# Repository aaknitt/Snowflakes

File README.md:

# ESP8266 Snowflakes
**KiCAD and FreeCAD files for RGB(W) snowflakes**

KiCAD schematic and PCB layout files (along with associated Gerber files) for ESP8266-based RGB(W) snowflakes.  

FreeCAD files for 3D printed diffuser (use clear filament).

Each snowflake uses 25 SK6812 (for RGBW) or WS2812b pixels.
Can be operated using the fantastic [ESPixelStick firmware](https://github.com/forkineye/ESPixelStick) in conjunction with a program such as XLights64.

Unmodified ESPixelStick firmware should work with RBG pixels.

If using RGBW pixels, modified firmware is necessary (I may put up a fork at some point in the future).

**Note:**  I have not actually made a batch of PCBs from these exact files.  I built PCBs using an earlier version, and these files include all of the changes I've made to correct mistakes in the original batch.  Use at your own risk!

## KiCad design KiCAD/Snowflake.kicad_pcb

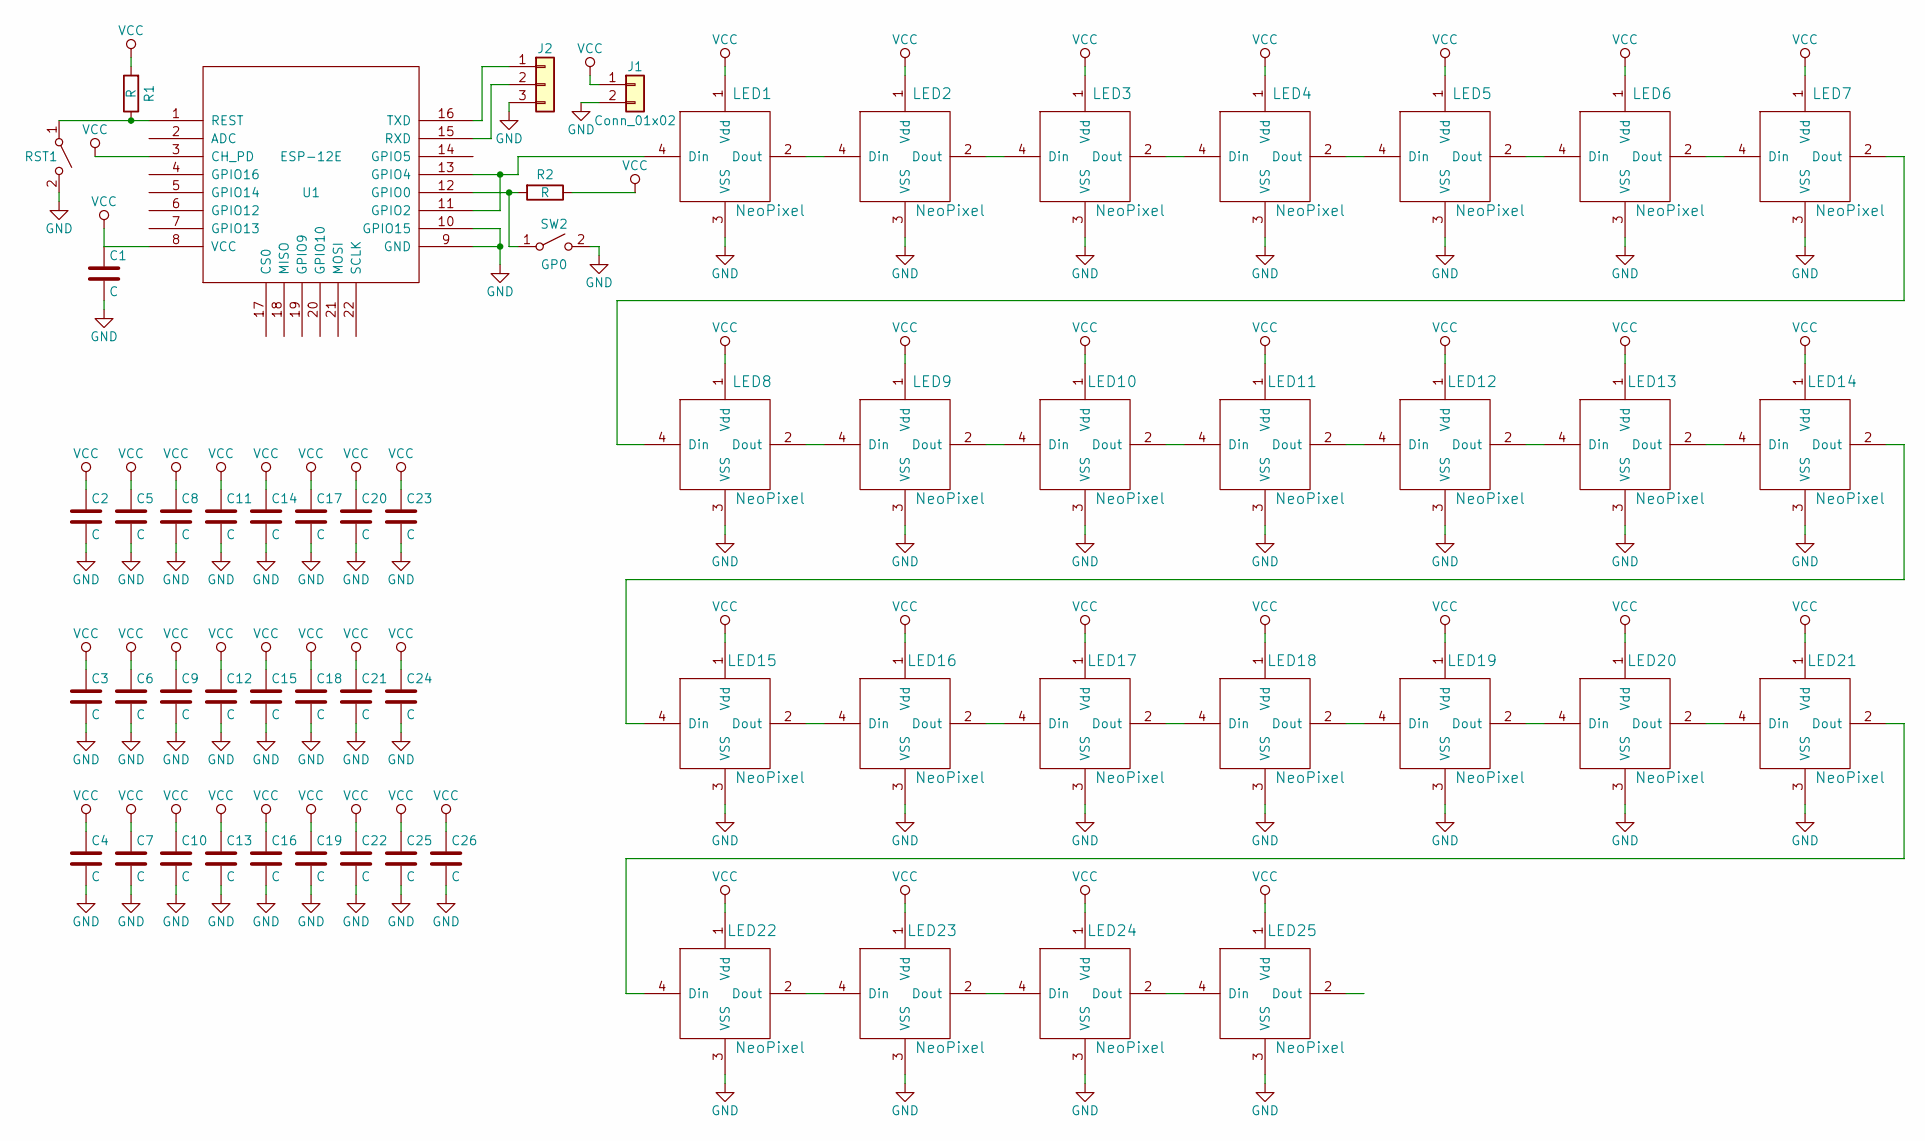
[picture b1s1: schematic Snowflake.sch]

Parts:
C1, C2, C3, C4, C5, C6, C7, C8, C9, C10, C11, C12, C13, C14, C15, C16, C17, C18, C19, C20, C21, C22, C23, C24, C25, C26: C; C_0805_HandSoldering
J1: Conn_01x02; SolderWirePad_2x_1-2mmDrill
J2: Conn_01x03; Pin_Header_Straight_1x03_Pitch2.54mm
LED1, LED2, LED3, LED4, LED5, LED6, LED7, LED8, LED9, LED10, LED11, LED12, LED13, LED14, LED15, LED16, LED17, LED18, LED19, LED20, LED21, LED22, LED23, LED24, LED25: NeoPixel; LED_WS2812B-PLCC4
R1, R2: R; R_0805_HandSoldering
RST1: SW_SPST; SW_SPST_KMR2
SW2: GP0; SW_SPST_KMR2
U1: ESP-12E; ESP-12E_SMD

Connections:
GND: C1.2, C2.2, C3.2, C4.2, C5.2, C6.2, C7.2, C8.2, C9.2, C10.2, C11.2, C12.2, C13.2, C14.2, C15.2, C16.2, C17.2, C18.2, C19.2, C20.2, C21.2, C22.2, C23.2, C24.2, C25.2, C26.2, J1.2, J2.3, LED1.3 (VSS), LED2.3 (VSS), LED3.3 (VSS), LED4.3 (VSS), LED5.3 (VSS), LED6.3 (VSS), LED7.3 (VSS), LED8.3 (VSS), LED9.3 (VSS), LED10.3 (VSS), LED11.3 (VSS), LED12.3 (VSS), LED13.3 (VSS), LED14.3 (VSS), LED15.3 (VSS), LED16.3 (VSS), LED17.3 (VSS), LED18.3 (VSS), LED19.3 (VSS), LED20.3 (VSS), LED21.3 (VSS), LED22.3 (VSS), LED23.3 (VSS), LED24.3 (VSS), LED25.3 (VSS), RST1.2 (B), SW2.2 (B), U1.9 (GND), U1.10 (GPIO15)
unnamed: J2.1, U1.16 (TXD)
unnamed: J2.2, U1.15 (RXD)
unnamed: LED1.2 (Dout), LED2.4 (Din)
unnamed: LED1.4 (Din), U1.11 (GPIO2), U1.13 (GPIO4)
unnamed: LED2.2 (Dout), LED3.4 (Din)
unnamed: LED3.2 (Dout), LED4.4 (Din)
unnamed: LED4.2 (Dout), LED5.4 (Din)
unnamed: LED5.2 (Dout), LED6.4 (Din)
unnamed: LED6.2 (Dout), LED7.4 (Din)
unnamed: LED7.2 (Dout), LED8.4 (Din)
unnamed: LED8.2 (Dout), LED9.4 (Din)
unnamed: LED10.2 (Dout), LED11.4 (Din)
unnamed: LED9.2 (Dout), LED10.4 (Din)
unnamed: LED11.2 (Dout), LED12.4 (Din)
unnamed: LED12.2 (Dout), LED13.4 (Din)
unnamed: LED13.2 (Dout), LED14.4 (Din)
unnamed: LED14.2 (Dout), LED15.4 (Din)
unnamed: LED15.2 (Dout), LED16.4 (Din)
unnamed: LED16.2 (Dout), LED17.4 (Din)
unnamed: LED17.2 (Dout), LED18.4 (Din)
unnamed: LED18.2 (Dout), LED19.4 (Din)
unnamed: LED19.2 (Dout), LED20.4 (Din)
unnamed: LED20.2 (Dout), LED21.4 (Din)
unnamed: LED21.2 (Dout), LED22.4 (Din)
unnamed: LED22.2 (Dout), LED23.4 (Din)
unnamed: LED23.2 (Dout), LED24.4 (Din)
unnamed: LED24.2 (Dout), LED25.4 (Din)
unnamed: R1.1, RST1.1 (A), U1.1 (REST)
unnamed: R2.2, SW2.1 (A), U1.12 (GPIO0)
VCC: C1.1, C2.1, C3.1, C4.1, C5.1, C6.1, C7.1, C8.1, C9.1, C10.1, C11.1, C12.1, C13.1, C14.1, C15.1, C16.1, C17.1, C18.1, C19.1, C20.1, C21.1, C22.1, C23.1, C24.1, C25.1, C26.1, J1.1, LED1.1 (Vdd), LED2.1 (Vdd), LED3.1 (Vdd), LED4.1 (Vdd), LED5.1 (Vdd), LED6.1 (Vdd), LED7.1 (Vdd), LED8.1 (Vdd), LED9.1 (Vdd), LED10.1 (Vdd), LED11.1 (Vdd), LED12.1 (Vdd), LED13.1 (Vdd), LED14.1 (Vdd), LED15.1 (Vdd), LED16.1 (Vdd), LED17.1 (Vdd), LED18.1 (Vdd), LED19.1 (Vdd), LED20.1 (Vdd), LED21.1 (Vdd), LED22.1 (Vdd), LED23.1 (Vdd), LED24.1 (Vdd), LED25.1 (Vdd), R1.2, R2.1, U1.3 (CH_PD), U1.8 (VCC)

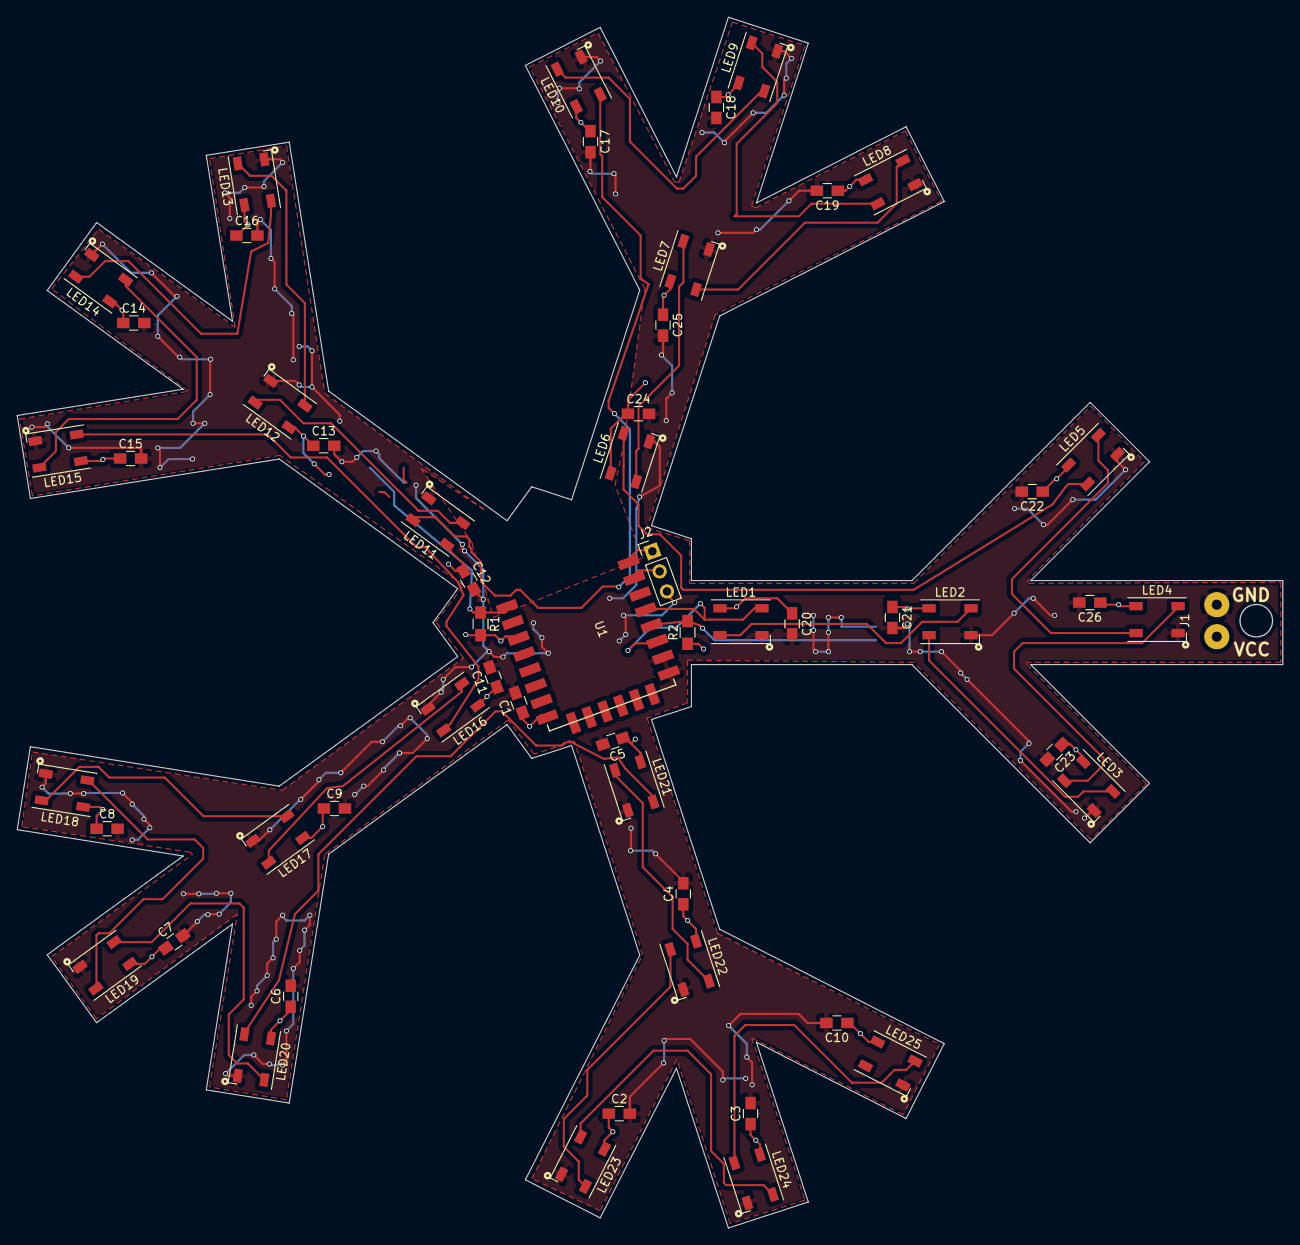
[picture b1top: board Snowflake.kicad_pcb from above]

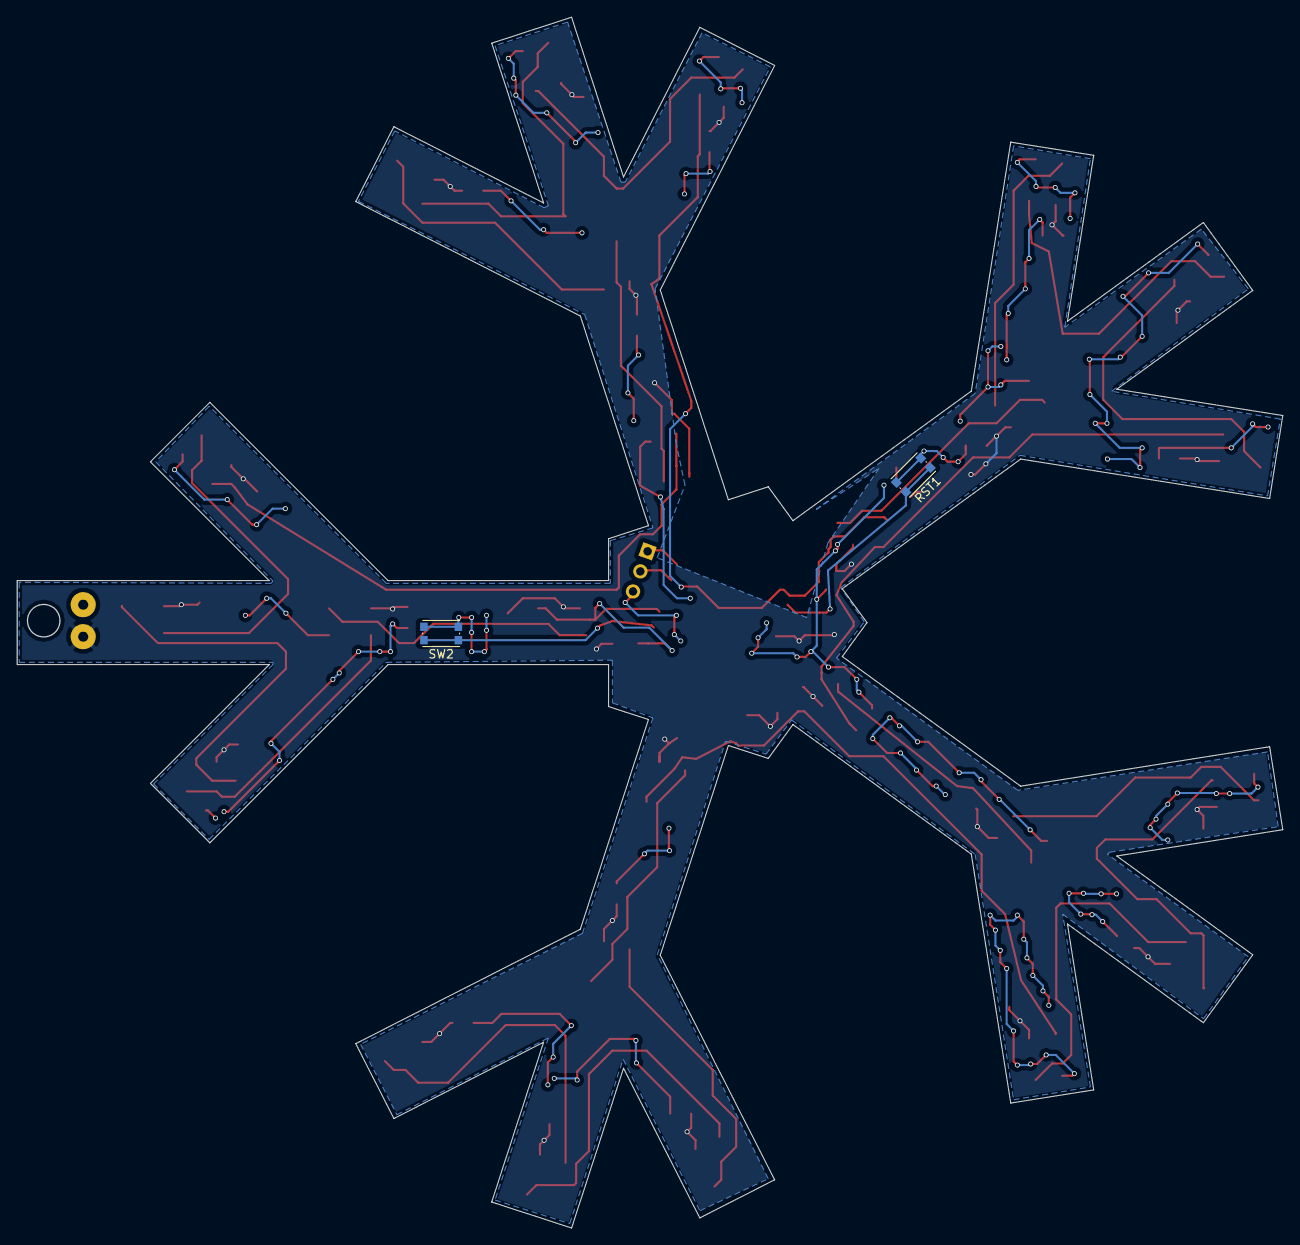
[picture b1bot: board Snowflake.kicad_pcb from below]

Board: 2 copper layers, 150.6 x 144.1 mm, 58 parts (2 on the bottom side), 31 nets.

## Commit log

2018-12-29 Added FreeCAD files
2018-12-29 Added folder structure
2018-12-29 Added pictures
